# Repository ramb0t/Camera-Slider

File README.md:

# Camera-Slider
Stepper motor driven camera slider controlled with Arduino + OLED + rotary encoder

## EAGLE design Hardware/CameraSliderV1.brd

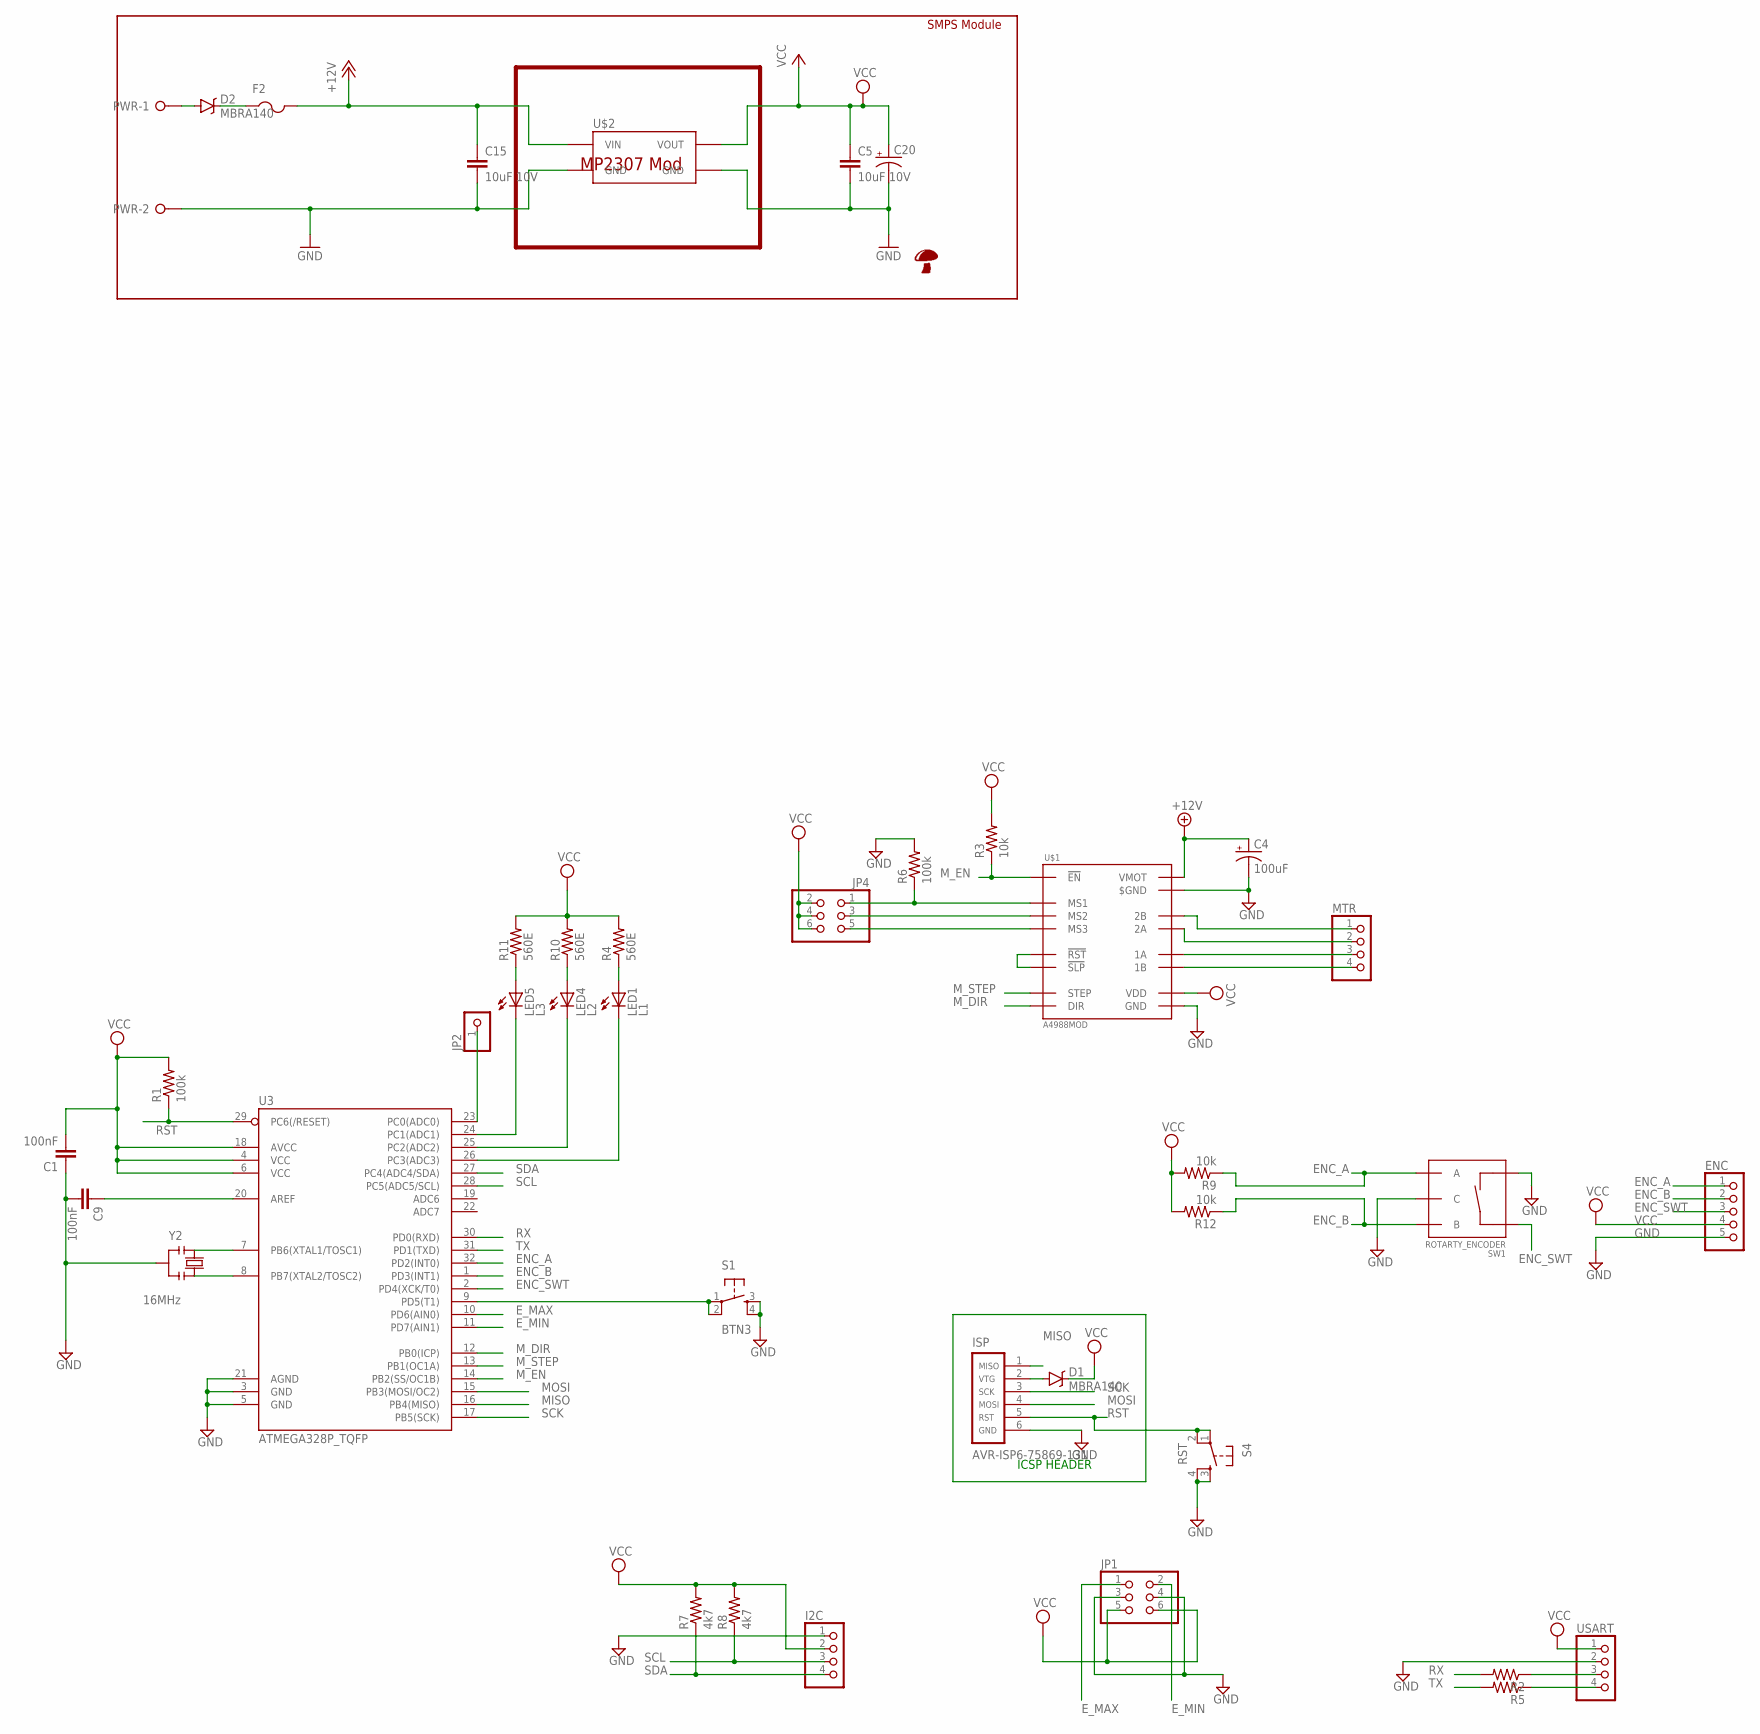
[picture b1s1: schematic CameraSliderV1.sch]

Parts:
C1, C9: 100nF; C0805
C4: 100uF; PANASONIC_D
C5, C15: 10uF 10V; C0805
C20: CPOL-USD; PANASONIC_D
D1, D2: MBRA140; SMA-DIODE
ENC: PINHD-1X5; 1X05
F2: PTCFUSE-1812; 1812
I2C: PINHD-1X4; 1X04
ISP: AVR-ISP6-75869-131; HDR-75869-131
JP1, JP4: PINHD-2X3; 2X03
JP2: PINHD-1X1; 1X01
LED1: L1; CHIP-LED0805
LED4: L2; CHIP-LED0805
LED5: L3; CHIP-LED0805
MTR: PINHD-1X4; 1X04
PWR: W237-02P; W237-132
R1, R6: 100k; M0805
R2, R5: R-US_M0805; M0805
R3, R9, R12: 10k; M0805
R4, R10, R11: 560E; M0805
R7, R8: 4k7; M0805
S1: BTN3; TACTILE_SWITCH_SMD
S4: RST; TACTILE_SWITCH_SMD
SW1: ROTARTY_ENCODER; ROTARY_ENC_PLAIN
U3: ATMEGA328P_TQFP; TQFP32-08
U$1: A4988MOD
U$2: MP1584_MODULE; D-SUN_MP1584
U$15: SHROOM5MM; SHROOM
USART: PINHD-1X4; 1X04
Y2: 16MHz; RESONATOR

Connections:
+12V: C4.+, C15.1, F2.2, U$1.P$16 (VMOT), U$2.P$5 (VIN), U$2.P$6 (VIN)
ENC_A: ENC.1, R9.1, SW1.A, U3.32 (PD2(INT0))
ENC_B: ENC.2, R12.1, SW1.B, U3.1 (PD3(INT1))
ENC_SWT: ENC.3, SW1.SW+, U3.2 (PD4(XCK/T0))
E_MAX: JP1.1, U3.10 (PD6(AIN0))
E_MIN: JP1.2, U3.11 (PD7(AIN1))
GND: C1.1, C4.-, C5.2, C9.2, C15.2, C20.-, ENC.5, I2C.1, ISP.6, JP1.3, JP1.4, PWR.2, R6.2, S1.3, S1.4, S4.3, S4.4, SW1.C, SW1.SW-, U3.3 (GND), U3.5 (GND), U3.21 (AGND), U$1.P$9 (GND), U$1.P$15 ($GND), U$2.P$1 (GND), U$2.P$2 (GND), U$2.P$3 (GND), U$2.P$4 (GND), USART.2, Y2.2
MISO: ISP.1, U3.16 (PB4(MISO))
MOSI: ISP.4, U3.15 (PB3(MOSI/OC2))
M_DIR: U3.12 (PB0(ICP)), U$1.P$8 (DIR)
M_EN: R3.1, U3.14 (PB2(SS/OC1B)), U$1.P$1 (!EN)
M_STEP: U3.13 (PB1(OC1A)), U$1.P$7 (STEP)
unnamed: LED1.A, R4.1
unnamed: D1.A, ISP.2
unnamed: LED5.C, U3.24 (PC1(ADC1))
unnamed: JP4.1, R6.1, U$1.P$2 (MS1)
unnamed: U3.7 (PB6(XTAL1/TOSC1)), Y2.1
unnamed: U3.8 (PB7(XTAL2/TOSC2)), Y2.3
unnamed: LED4.A, R10.1
unnamed: LED5.A, R11.1
unnamed: LED4.C, U3.25 (PC2(ADC2))
unnamed: LED1.C, U3.26 (PC3(ADC3))
unnamed: S1.1, S1.2, U3.9 (PD5(T1))
unnamed: MTR.2, U$1.P$13 (2A)
unnamed: R2.1, USART.3
unnamed: R5.1, USART.4
unnamed: C9.1, U3.20 (AREF)
unnamed: MTR.1, U$1.P$14 (2B)
unnamed: MTR.3, U$1.P$12 (1A)
unnamed: MTR.4, U$1.P$11 (1B)
unnamed: JP4.3, U$1.P$3 (MS2)
unnamed: JP4.5, U$1.P$4 (MS3)
unnamed: U$1.P$5 (!RST), U$1.P$6 (!SLP)
unnamed: D2.A, PWR.1
unnamed: JP2.1, U3.23 (PC0(ADC0))
unnamed: D2.C, F2.1
RST: ISP.5, R1.1, S4.1, S4.2, U3.29 (PC6(/RESET))
RX: R2.2, U3.30 (PD0(RXD))
SCK: ISP.3, U3.17 (PB5(SCK))
SCL: I2C.3, R8.1, U3.28 (PC5(ADC5/SCL))
SDA: I2C.4, R7.1, U3.27 (PC4(ADC4/SDA))
TX: R5.2, U3.31 (PD1(TXD))
VCC: C1.2, C5.1, C20.+, D1.C, ENC.4, I2C.2, JP1.5, JP1.6, JP4.2, JP4.4, JP4.6, R1.2, R3.2, R4.2, R7.2, R8.2, R9.2, R10.2, R11.2, R12.2, U3.4 (VCC), U3.6 (VCC), U3.18 (AVCC), U$1.P$10 (VDD), U$2.P$7 (VOUT), U$2.P$8 (VOUT), USART.1

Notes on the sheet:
ICSP HEADER
MP2307 Mod
SMPS Module

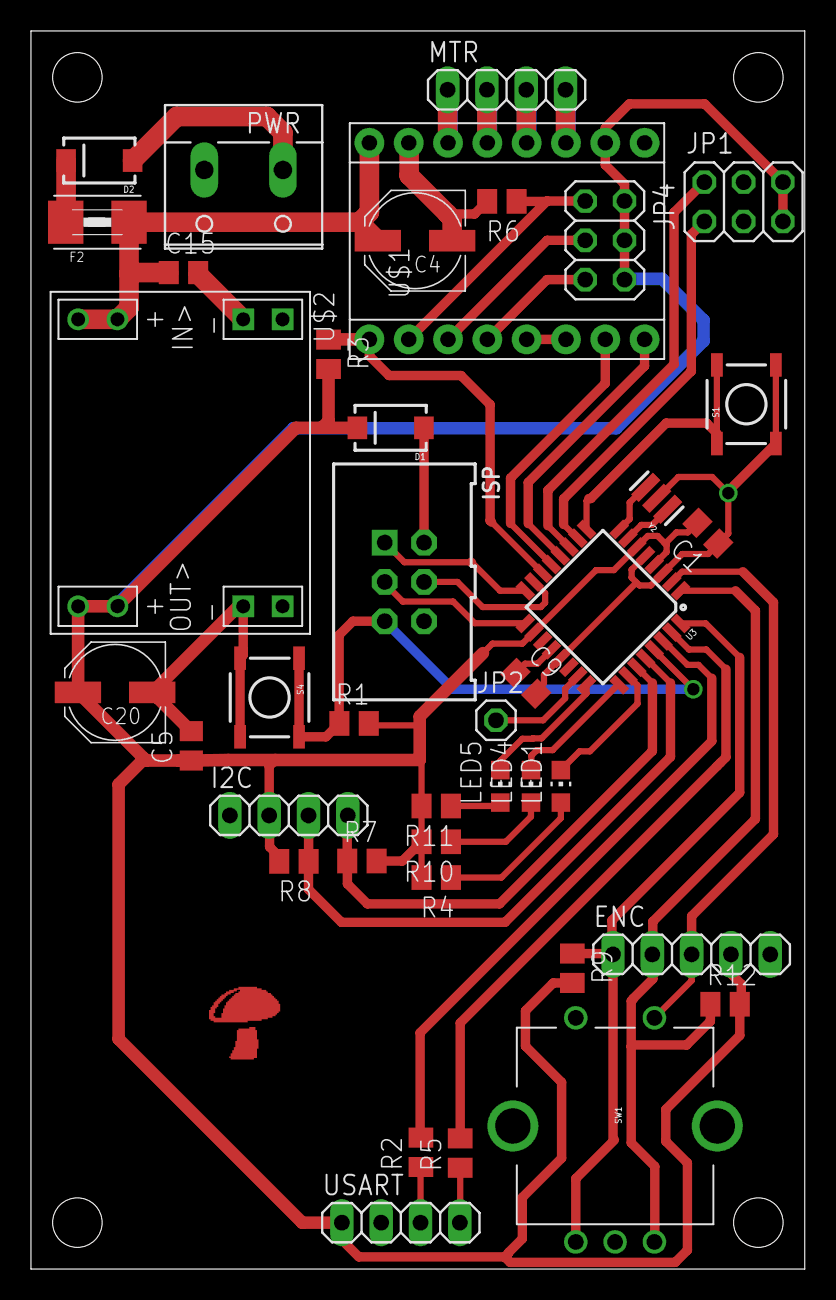
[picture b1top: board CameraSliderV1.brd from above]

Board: 2 copper layers, 50.0 x 80.0 mm, 41 parts (0 on the bottom side), 43 nets.

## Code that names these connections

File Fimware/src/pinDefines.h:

#ifndef PINDEFINES_H_
#define PINDEFINES_H_

#define LEDR A1 //AVR 24 PC1
#define LEDG A2 //AVR 25 PC2
#define LEDB A3 //AVR 26 PC3

#define ENCA 2  //AVR 32 PD2
#define ENCB 3  //AVR 1  PD3
#define ENCS 4  //AVR 2  PD4

#define BTN1 5  //AVR 9  PD5

#define EMAX 6  //AVR 10   PD6
#define EMIN 7  //AVR 11 PD7

#define SDIR 8  //AVR 12 PB0
#define SSTP 9  //AVR 13 PB1
#define SEN 10  //AVR 14 PB2

#define OLED_RESET A0 //AVR 23 PC0
#define SDA A4  //AVR 27 PC4
#define SCL A5  //AVR 28 PC5

// All the wires needed for full functionality
#define DIR SDIR
#define STEP SSTP

#endif /* PINDEFINES_H_ */

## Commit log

2017-01-25 Started on Time OLED screen
2017-01-25 Time code
2017-01-25 Display read, need math!
2017-01-25 Need to do running code
2017-02-03 Timing code added
2017-02-28 Something has gone wrong?
2017-02-28 baddymcbadstuff
2017-02-28 Worked on debug code...
2017-02-28 working with no debug...
2017-03-06 Need to work on timing code...
2017-03-06 Fixed running code
2017-03-06 Working! needs a clean tho
2017-03-07 home min code
2017-03-07 More code improvments, motor disable etc
2017-03-07 Working code, need to fix calibration now
2017-03-07 Calibration improved?
2017-03-07 Some calibration tweaks
2017-03-07 Working on debug code, needs testing now..
2017-03-10 Endstop code ?
2017-03-10 fixed default vals for oled display
2017-03-10 small update
2017-03-10 Beta1 ?
2017-09-11 Quick update

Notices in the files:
parts and their libraries:
SparkFun-DiscreteSemi: Licensing: Creative Commons ShareAlike 4.0 International - https://creativecommons.org/licenses/by-sa/4.0
atmel-avr: Copyright (C) 2008, Bob Starr
SparkFun: Licensing: CC v3.0 Share-Alike You are welcome to use this library for commercial purposes.
